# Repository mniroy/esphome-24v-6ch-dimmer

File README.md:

# 24V DC 6-Channel LAN ESPHome LED Dimmer (REV 1.2 DIN)

An open-source, DIN-rail friendly, high-power 24V DC 6-channel LED dimmer designed for **ESPHome** and **Home Assistant**. Engineered as a high-capacity, modular alternative to the **IKEA SILVERGLANS / TRÅDFRI** drivers, powered by an external 24V DC power supply.

---

## Key Features

- **6 Independent High-Power Channels**:
  - **48W – 60W per channel** (`2.0A – 2.5A` continuous @ 24V).
  - Up to **15A / 360W total continuous capacity**.
  - High-efficiency **AOD4184A** N-Channel logic-level MOSFETs in TO-252 (DPAK) with ultra-low $R_{DS(on)} < 9.5\text{ m}\Omega$ (~59 mW dissipation per channel @ 2.5A, cool running without external heat sinks).
- **Smooth Natural Dimming (IKEA SILVERGLANS Behavior)**:
  - Hardware LEDC PWM at **19.531 kHz** (ultrasonic, camera flicker-free, zero audible coil whine).
  - True gamma correction curve ($\gamma = 2.8$) for natural low-light perception.
  - Smooth default soft-transition on/off (600ms).
- **Modular ESP32 Controller**:
  - Socketed via two `1x15` 2.54mm female headers for standard **ESP32 DevKit V1 30-Pin (USB-C)**.
  - Easily swappable in seconds without desoldering.
  - Onboard USB-C on the dev board remains accessible on the bottom edge for programming/debugging.
- **Wired Ethernet LAN Connectivity**:
  - Onboard **WIZnet W5500** SPI TCP/IP controller + **HanRun HR911105A** RJ45 MagJack with internal magnetics and status LEDs.
  - Dedicated **AMS1117-3.3** LDO regulator for the Ethernet subsystem to ensure noise-free Wi-Fi/LAN operation.
- **DIN-Rail Friendly Form Factor**:
  - Dimensions: **152.0 mm × 72.0 mm** (fits standard **UM72** DIN-rail profile carriers).
  - 4x M3 mounting holes (3.2 mm diameter).
  - **Top-Facing Ports**: RJ45 Ethernet (`J_LAN`) and 24V DC Power Input (`J1`).
  - **Bottom-Facing Ports**: 6x 2-pin Screw Terminals (`CH1`–`CH6`) and USB-C port.
  - Left and right edges are 100% free of protruding connectors, allowing tight side-by-side DIN-rail packing.
- **Industrial-Grade Protection**:
  - Reverse Polarity Protection via high-current P-Channel MOSFET (**AOD403**) + 12V Zener gate clamp (**BZT52C12**).
  - **15A Mini Automotive Blade Fuse** (`F1`) with Keystone 3568 holder.
  - **SMBJ28A** TVS diode for clamping high-voltage inductive switching spikes.
  - 6x **SS34** 3A 40V Schottky flyback diodes across each channel output.
  - High-capacitance bulk filtering: Low-ESR 470µF 35V electrolytic + 10µF MLCC + 100nF decoupling.
- **Onboard Power Step-Down**:
  - **XL1509-5.0** 2A buck converter stepping 24V down to 5V to power the ESP32 dev board and the Ethernet 3.3V LDO.
- **Clear Silkscreen & Indonesian Market Component Availability**:
  - Bold `+` and `-` polarity indicators printed directly in front of each terminal block on both Top (`F.SilkS`) and Bottom (`B.SilkS`) layers.
  - All parts selected from common components readily available in Indonesia (Tokopedia / Shopee).

---

## Hardware Architecture & Pinout

### ESP32 Socket (`U2`, 30-Pin DevKit V1) Pinout

| ESP32 Pin | Socket Pad | Signal Name | Target | Function |
|---|---|---|---|---|
| **GPIO32** | Pad 6 | `ETH_RST` | W5500 Pin 37 (`RSTn`) | Ethernet Hardware Reset |
| **GPIO33** | Pad 7 | `ETH_INT` | W5500 Pin 36 (`INTn`) | Ethernet Interrupt |
| **GPIO25** | Pad 8 | `ETH_MISO` | W5500 Pin 34 (`MISO`) | SPI Master In Slave Out |
| **GPIO26** | Pad 9 | `ETH_MOSI` | W5500 Pin 35 (`MOSI`) | SPI Master Out Slave In |
| **GPIO27** | Pad 10 | `ETH_CS` | W5500 Pin 33 (`SCSn`) | SPI Chip Select |
| **GPIO14** | Pad 11 | `ETH_CLK` | W5500 Pin 32 (`SCLK`) | SPI Clock (20 MHz) |
| **GPIO16** | Pad 21 | `PWM_CH1` | Gate Q1 (`AOD4184A`) | Dimmer Channel 1 Output |
| **GPIO17** | Pad 22 | `PWM_CH2` | Gate Q2 (`AOD4184A`) | Dimmer Channel 2 Output |
| **GPIO18** | Pad 24 | `PWM_CH3` | Gate Q3 (`AOD4184A`) | Dimmer Channel 3 Output |
| **GPIO19** | Pad 25 | `PWM_CH4` | Gate Q4 (`AOD4184A`) | Dimmer Channel 4 Output |
| **GPIO21** | Pad 26 | `PWM_CH5` | Gate Q5 (`AOD4184A`) | Dimmer Channel 5 Output |
| **GPIO22** | Pad 29 | `PWM_CH6` | Gate Q6 (`AOD4184A`) | Dimmer Channel 6 Output |
| **5V / VIN**| Pad 15 | `+5V` | XL1509 Output / AMS1117 Input | Logic 5V Supply Rail |
| **GND** | Pad 14, 17 | `GND` | Ground Plane | System Common Ground |

---

## ESPHome Firmware Setup

The firmware configuration is located in [`firmware/dimmer_6ch.yaml`](firmware/dimmer_6ch.yaml).

### Compile & Flash
```bash
# Via USB-C (first-time flash)
esphome run firmware/dimmer_6ch.yaml

# Subsequent updates can be performed over Ethernet (OTA)
esphome run firmware/dimmer_6ch.yaml
```

Once flashed, 6 individual light entities (`light.dimmer_ch1` through `light.dimmer_ch6`) will automatically discover in Home Assistant with complete brightness control, soft on/off fading, and status persistence.

---

## Manufacturing & Ordering on JLCPCB

Pre-packaged, verified files ready for 1-click drag-and-drop ordering on [JLCPCB](https://jlcpcb.com):

### 1. Bare PCB Fabrication
- **Direct Upload File**: [`manufacturing/jlcpcb/GERBER-dimmer_6ch.zip`](manufacturing/jlcpcb/GERBER-dimmer_6ch.zip)
  - Simply drag & drop `GERBER-dimmer_6ch.zip` into the JLCPCB quote page.
  - Automatically detected specs: 2-layer FR-4, **152.0 mm × 72.0 mm**, 1.6mm thickness, 1oz copper, green solder mask / white silkscreen.

### 2. SMT Assembly (PCBA)
When enabling **PCB Assembly** on JLCPCB:
- **BOM File**: [`manufacturing/jlcpcb/BOM-dimmer_6ch.csv`](manufacturing/jlcpcb/BOM-dimmer_6ch.csv) (includes pre-matched **LCSC Part Numbers** for 100% automated part recognition).
- **CPL / Centroid File**: [`manufacturing/jlcpcb/CPL-dimmer_6ch.csv`](manufacturing/jlcpcb/CPL-dimmer_6ch.csv) (precise metric coordinates and rotation for pick-and-place machines).

### 3. Source & Project Files
- **KiCad Project Files**: [`dimmer_6ch.kicad_pro`](dimmer_6ch.kicad_pro), [`dimmer_6ch.kicad_pcb`](dimmer_6ch.kicad_pcb).
- **Python Export Automation**: [`manufacturing/export_jlcpcb.py`](manufacturing/export_jlcpcb.py).
- **DRC Verification**: 0 electrical violations, 0 unconnected items ([`drc_report.json`](drc_report.json)).

---

## License
Open-source hardware licensed under the CERN-OHL-P v2 (or MIT for accompanying software/firmware).

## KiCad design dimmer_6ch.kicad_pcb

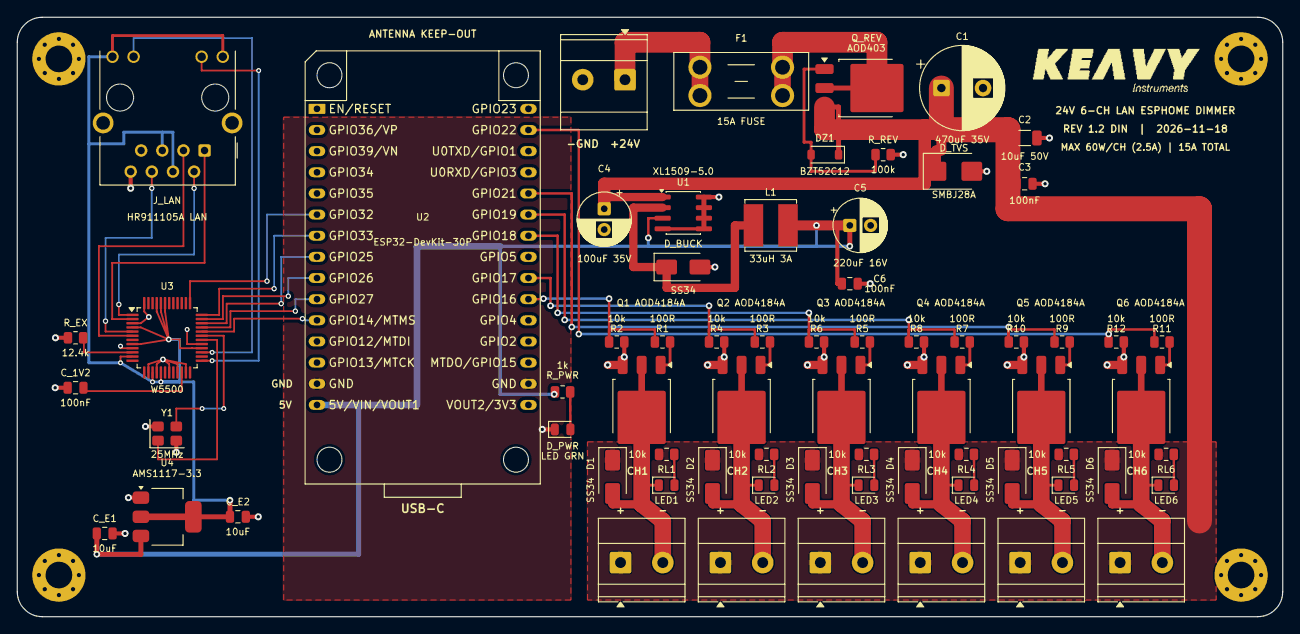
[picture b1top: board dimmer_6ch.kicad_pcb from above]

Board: 2 copper layers, 152.0 x 72.0 mm, 72 parts (0 on the bottom side), 49 nets.

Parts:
C1: 470uF 35V; CP_Radial_D10.0mm_P5.00mm
C2: 10uF 50V; C_1206_3216Metric
C3, C6: 100nF; C_0805_2012Metric
C4: 100uF 35V; CP_Radial_D6.3mm_P2.50mm
C5: 220uF 16V; CP_Radial_D6.3mm_P2.50mm
C_1V2: 100nF; C_0805_2012Metric
C_E1, C_E2: 10uF; C_0805_2012Metric
D1, D2, D3, D4, D5, D6: SS34; D_SMA
DZ1: BZT52C12; D_SOD-123
D_BUCK: SS34; D_SMA
D_PWR: LED GRN; LED_0805_2012Metric
D_TVS: SMBJ28A; D_SMB
F1: 15A FUSE; Fuseholder_Blade_Mini_Keystone_3568
H1, H2, H3, H4: M3; MountingHole_3.2mm_M3_Pad_Via
J1: 24V_IN; TerminalBlock_Phoenix_MKDS-3-2-5.08_1x02_P5.08mm_Horizontal
J2: CH1; TerminalBlock_Phoenix_MKDS-1,5-2-5.08_1x02_P5.08mm_Horizont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
J3: CH2; TerminalBlock_Phoenix_MKDS-1,5-2-5.08_1x02_P5.08mm_Horizont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
J4: CH3; TerminalBlock_Phoenix_MKDS-1,5-2-5.08_1x02_P5.08mm_Horizont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
J5: CH4; TerminalBlock_Phoenix_MKDS-1,5-2-5.08_1x02_P5.08mm_Horizont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
J6: CH5; TerminalBlock_Phoenix_MKDS-1,5-2-5.08_1x02_P5.08mm_Horizont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
J7: CH6; TerminalBlock_Phoenix_MKDS-1,5-2-5.08_1x02_P5.08mm_Horizont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
J_LAN: HR911105A LAN; RJ45_Hanrun_HR911105A_Horizontal
L1: 33uH 3A; L_Bourns_SRN6045TA
LED1, LED2, LED3, LED4, LED5, LED6: LED; LED_0805_2012Metric
Q1, Q2, Q3, Q4, Q5, Q6: AOD4184A; TO-252-3_TabPin2
Q_REV: AOD403; TO-252-3_TabPin2
R1, R3, R5, R7, R9, R11: 100R; R_0805_2012Metric
R2, R4, R6, R8, R10, R12: 10k; R_0805_2012Metric
RL1, RL2, RL3, RL4, RL5, RL6: 10k; R_0805_2012Metric
R_EX: 12.4k; R_0805_2012Metric
R_PWR: 1k; R_0805_2012Metric
R_REV: 100k; R_0805_2012Metric
U1: XL1509-5.0; SOIC-8_3.9x4.9mm_P1.27mm
U2: ESP32-DevKit-30P; ESP32-DevKit-USB-C
U3: W5500; LQFP-48_7x7mm_P0.5mm
U4: AMS1117-3.3; SOT-223-3_TabPin2
Y1: 25MHz; Crystal_SMD_3225-4Pin_3.2x2.5mm

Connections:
+3V3_ETH: C_E2.1, J_LAN.4, J_LAN.5, J_LAN.9, J_LAN.12, U3.4, U3.8, U3.11, U3.15, U3.17, U3.28, U3.43, U3.44, U3.45, U4.2
+5V: C5.1, C6.1, C_E1.1, L1.2, R_PWR.1, U1.3, U2.15, U4.3
+24V_BUS: C1.1, C2.1, C3.1, C4.1, D1.1, D2.1, D3.1, D4.1, D5.1, D6.1, DZ1.1, D_TVS.1, J2.1, J3.1, J4.1, J5.1, J6.1, J7.1, Q_REV.3, RL1.1, RL2.1, RL3.1, RL4.1, RL5.1, RL6.1, U1.1
+24V_FUSED: F1.2, Q_REV.2
+24V_IN: F1.1, J1.1
BUCK_SW: D_BUCK.1, L1.1, U1.2
CH1_OUT-: D1.2, J2.2, LED1.1, Q1.2
CH2_OUT-: D2.2, J3.2, LED2.1, Q2.2
CH3_OUT-: D3.2, J4.2, LED3.1, Q3.2
CH4_OUT-: D4.2, J5.2, LED4.1, Q4.2
CH5_OUT-: D5.2, J6.2, LED5.1, Q5.2
CH6_OUT-: D6.2, J7.2, LED6.1, Q6.2
ETH_1V2O: C_1V2.1, U3.22
ETH_ACT_LED: J_LAN.11, U3.27
ETH_CLK: U2.11, U3.32
ETH_CS: U2.10, U3.33
ETH_EXRES: R_EX.1, U3.10
ETH_INT: U2.7, U3.36
ETH_LINK_LED: J_LAN.10, U3.25
ETH_MISO: U2.8, U3.34
ETH_MOSI: U2.9, U3.35
ETH_RST: U2.6, U3.37
ETH_RXN: J_LAN.6, U3.5
ETH_RXP: J_LAN.3, U3.6
ETH_TXN: J_LAN.2, U3.1
ETH_TXP: J_LAN.1, U3.2
ETH_XI: U3.30, Y1.1
ETH_XO: U3.31, Y1.3
GATE_CH1: Q1.1, R1.2
GATE_CH2: Q2.1, R3.2
GATE_CH3: Q3.1, R5.2
GATE_CH4: Q4.1, R7.2
GATE_CH5: Q5.1, R9.2
GATE_CH6: Q6.1, R11.2
GND: C1.2, C2.2, C3.2, C4.2, C5.2, C6.2, C_1V2.2, C_E1.2, C_E2.2, D_BUCK.2, D_PWR.1, D_TVS.2, H1.1, H2.1, H3.1, H4.1, J1.2, J_LAN.8, J_LAN.SH, Q1.3, Q2.3, Q3.3, Q4.3, Q5.3, Q6.3, R2.2, R4.2, R6.2, R8.2, R10.2, R12.2, R_EX.2, R_REV.2, U1.4, U1.5, U1.6, U1.7, U1.8, U2.14, U2.17, U3.3, U3.9, U3.14, U3.16, U3.19, U3.21, U3.23, U3.29, U3.48, U4.1, Y1.2, Y1.4
LED_CH1_K: LED1.2, RL1.2
LED_CH2_K: LED2.2, RL2.2
LED_CH3_K: LED3.2, RL3.2
LED_CH4_K: LED4.2, RL4.2
LED_CH5_K: LED5.2, RL5.2
LED_CH6_K: LED6.2, RL6.2
PWM_CH1: R1.1, R2.1, U2.21
PWM_CH2: R3.1, R4.1, U2.22
PWM_CH3: R5.1, R6.1, U2.24
PWM_CH4: R7.1, R8.1, U2.25
PWM_CH5: R9.1, R10.1, U2.26
PWM_CH6: R11.1, R12.1, U2.29
PWR_LED_A: D_PWR.2, R_PWR.2
REV_GATE: DZ1.2, Q_REV.1, R_REV.1

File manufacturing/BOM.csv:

Reference,Quantity,Value,Footprint,Description
J1,1,24V_IN,TerminalBlock_Phoenix_MKDS-3-2-5.08_1x02_P5.08mm_Horizontal,24V DC Input Screw Terminal (2-pin 5.08mm)
J2-J7,6,CH1-CH6,TerminalBlock_Phoenix_MKDS-1,5-2-5.08_1x02_P5.08mm_Horizontal,24V LED Output Screw Terminal (2-pin 5.08mm)
J_LAN,1,HR911105A LAN,RJ45_Hanrun_HR911105A_Horizontal,HanRun HR911105A 10/100 RJ45 Ethernet MagJack (Tersedia luas di Tokopedia/Shopee)
U3,1,W5500,LQFP-48_7x7mm_P0.5mm,WIZnet W5500 Hardwired TCP/IP SPI Ethernet Controller
Y1,1,25MHz,Crystal_SMD_3225-4Pin_3.2x2.5mm,25MHz SMD Crystal Oscillator for W5500
R_EX,1,12.4k,R_0805_2012Metric,12.4k 1% Reference Resistor for W5500 EXRES1
C_1V2,1,100nF,C_0805_2012Metric,W5500 1.2V Internal Regulator Decoupling Capacitor
U4,1,AMS1117-3.3,SOT-223-3_TabPin2,Dedicated 3.3V LDO Regulator for W5500 Ethernet
C_E1,1,10uF,C_0805_2012Metric,AMS1117-3.3 Input Decoupling Capacitor (5V)
C_E2,1,10uF,C_0805_2012Metric,AMS1117-3.3 Output Decoupling Capacitor (3.3V ETH)
F1,1,15A FUSE,Fuseholder_Blade_Mini_Keystone_3568,Mini Automotive Blade Fuse Holder + 15A Fuse
Q_REV,1,AOD403,TO-252-3_TabPin2,P-Channel MOSFET Reverse Polarity Protection (DPAK)
DZ1,1,BZT52C12,D_SOD-123,12V Zener Diode Gate Clamp
R_REV,1,100k,R_0805_2012Metric,Reverse Polarity Gate Pull-Down Resistor
D_TVS,1,SMBJ28A,D_SMB,28V Transient Voltage Suppressor Diode
C1,1,470uF 35V,CP_Radial_D10.0mm_P5.00mm,24V Bulk Electrolytic Capacitor Low-ESR
C2,1,10uF 50V,C_1206_3216Metric,24V Ceramic Decoupling Capacitor
C3,1,100nF,C_0805_2012Metric,24V High-Frequency Decoupling Capacitor
C4,1,100uF 35V,CP_Radial_D6.3mm_P2.50mm,Buck Converter Input Electrolytic Capacitor
U1,1,XL1509-5.0,SOIC-8_3.9x4.9mm_P1.27mm,24V to 5V 2A Step-Down Buck Converter IC
D_BUCK,1,SS34,D_SMA,3A 40V Schottky Catch Diode
L1,1,33uH 3A,L_Bourns_SRN6045TA,Shielded SMD Power Inductor 33uH 3A
C5,1,220uF 16V,CP_Radial_D6.3mm_P2.50mm,5V Buck Output Electrolytic Capacitor
C6,1,100nF,C_0805_2012Metric,5V Output Decoupling Capacitor
R_PWR,1,1k,R_0805_2012Metric,5V Power LED Current Limiting Resistor
D_PWR,1,LED GRN,LED_0805_2012Metric,5V Power Indicator LED (Green)
U2,1,ESP32-DevKit-30P,ESP32-DevKit-USB-C + 2x PinSocket_1x15_P2.54mm,Modular 30-Pin ESP32 DevKit V1 USB-C (Socketed)
Q1-Q6,6,AOD4184A,TO-252-3_TabPin2,N-Channel Logic-Level Power MOSFET 40V 50A (<9.5mOhm)
"R1,R3,R5,R7,R9,R11",6,100R,R_0805_2012Metric,MOSFET Gate Series Resistor
"R2,R4,R6,R8,R10,R12",6,10k,R_0805_2012Metric,MOSFET Gate Pull-Down Resistor
D1-D6,6,SS34,D_SMA,3A 40V Flyback/Clamping Schottky Diode
RL1-RL6,6,10k,R_0805_2012Metric,Channel Status LED Resistor
LED1-LED6,6,LED,LED_0805_2012Metric,Channel Dimming Status LED
H1-H4,4,M3,MountingHole_3.2mm_M3_Pad_Via,M3 PCB Mounting Hole
